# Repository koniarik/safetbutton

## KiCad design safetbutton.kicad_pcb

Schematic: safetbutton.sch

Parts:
C1: 1.0uF; C_0805_2012Metric_Pad1.15x1.40mm_HandSolder
C2: 2.2uF; C_0805_2012Metric_Pad1.15x1.40mm_HandSolder
D1, D2: LED; D_0603_1608Metric_Pad1.05x0.95mm_HandSolder
J1: Conn_01x02_Male; PinHeader_1x02_P2.54mm_Vertical
J2: Conn_02x03_Odd_Even; PinHeader_2x03_P2.54mm_Vertical_SMD
J3: Conn_01x02_Male; AMASS_XT60-M_1x02_P7.20mm_Vertical
J4: Conn_01x02_Male; AMASS_XT60-F_1x02_P7.20mm_Vertical
J5, J6: Conn_01x01_Male; MountingHole_3.2mm_M3
Q1: Q_PMOS_GDSD; TO-220-3_Horizontal_TabDown
Q2: BSS138; SOT-23
R1, R2, R3, R4, R5, R6, R7, R8: R; R_0603_1608Metric_Pad1.05x0.95mm_HandSolder
TP1, TP2, TP3, TP4, TP5, TP7, TP8: TestPoint; TestPoint_Pad_1.0x1.0mm
U1: ATtiny85-20SU; SOIJ-8_5.3x5.3mm_P1.27mm
U2: AP2210N-3.3; SOT-23

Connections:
+3V3: C2.1, J2.2, R1.1, R4.1, R7.1, TP7.1, U1.8, U2.2
GND: C1.2, C2.2, J1.1, J2.6, J3.1, J4.1, Q2.2 (S), R6.2, R8.2, TP8.1, U1.4, U2.1
MISO: D1.1 (K), J2.1, TP2.1, U1.6
MOSI: D2.1 (K), J2.4, TP1.1, U1.5
unnamed: D1.2 (A), R4.2
unnamed: D2.2 (A), R7.2
unnamed: J4.2, Q1.2 (D), Q1.4 (D)
unnamed: Q1.1 (G), R2.2, R3.1
unnamed: Q2.3 (D), R3.2
OUT: Q2.1 (G), R8.1, TP4.1, U1.2
RST: J2.5, U1.1
S: J1.2, R1.2, TP5.1, U1.3
SCK: J2.3, R5.2, R6.1, TP3.1, U1.7
VCC: C1.1, J3.2, Q1.3 (S), R2.1, R5.1, U2.3

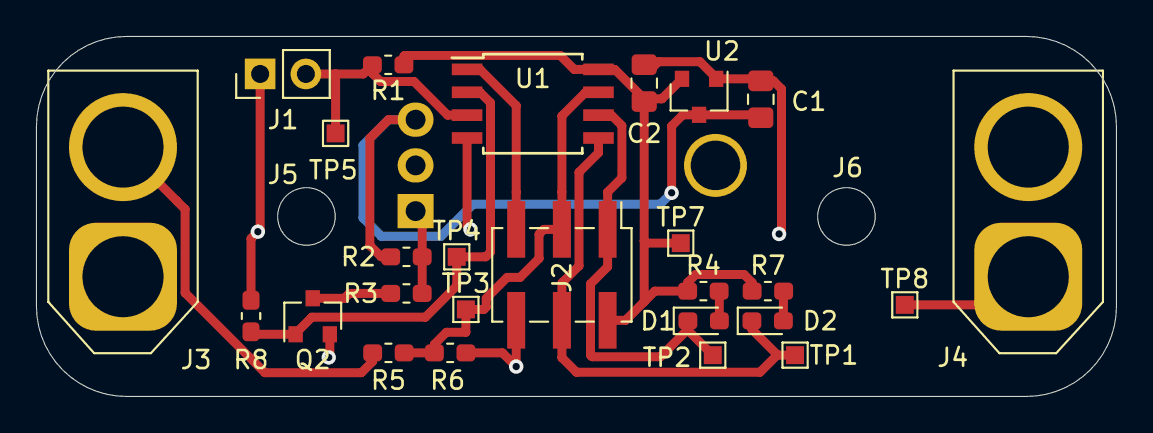
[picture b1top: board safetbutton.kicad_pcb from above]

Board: 2 copper layers, 60.0 x 20.0 mm, 29 parts (1 on the bottom side), 14 nets.

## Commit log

2020-08-13 vanilla
2020-08-13 le picture
2021-07-30 Fixed button handling
2021-07-30 Added .gitignore file
2021-08-06 Reworked the board to work with the BC805M module
